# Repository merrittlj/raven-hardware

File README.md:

<h1 align="center">
    <br>
    Raven - Hardware Repository
    <br>
</h1>

## About
This is the hardware repository for the Raven smartwatch. Versioning is completely independent of the firmware repository.

## License

Distributed under the GPLv3. See ['LICENSE'](LICENSE) for more info.

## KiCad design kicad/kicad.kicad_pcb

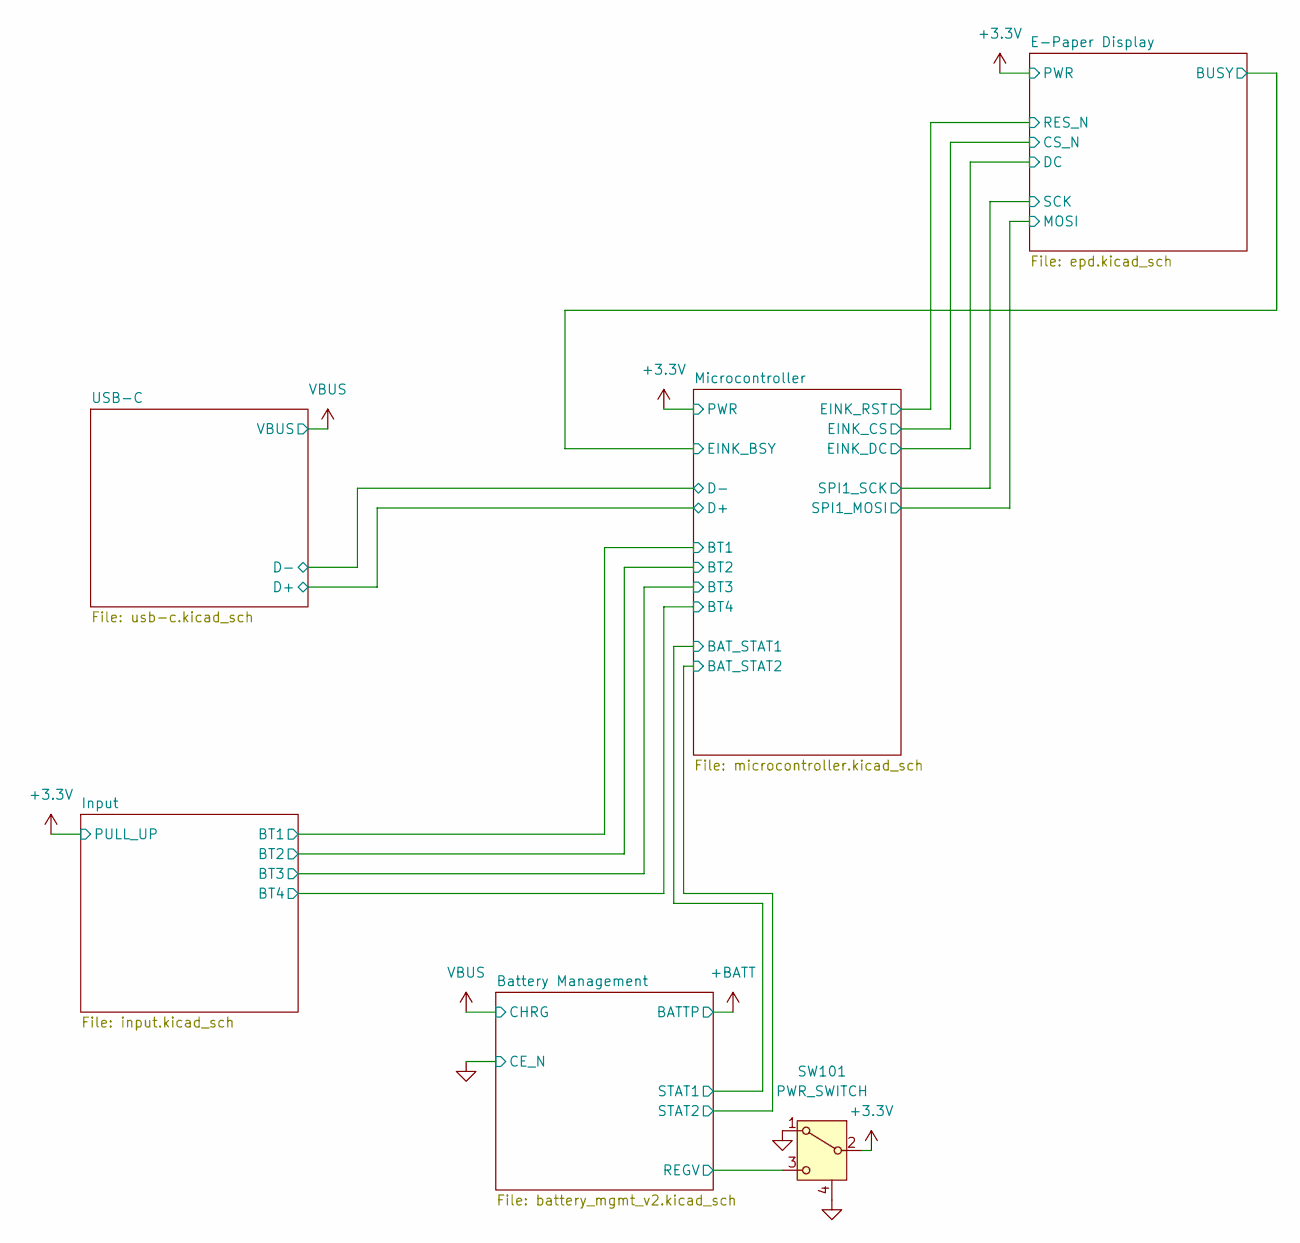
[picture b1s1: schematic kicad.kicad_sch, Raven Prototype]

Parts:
SW101: PWR_SWITCH; SSSS811101

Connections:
+3.3V: SW101.2 (B); also elsewhere on the board
/Battery Management/REGV: SW101.3 (C); also elsewhere on the board
GND: SW101.1 (A), SW101.4; also elsewhere on the board

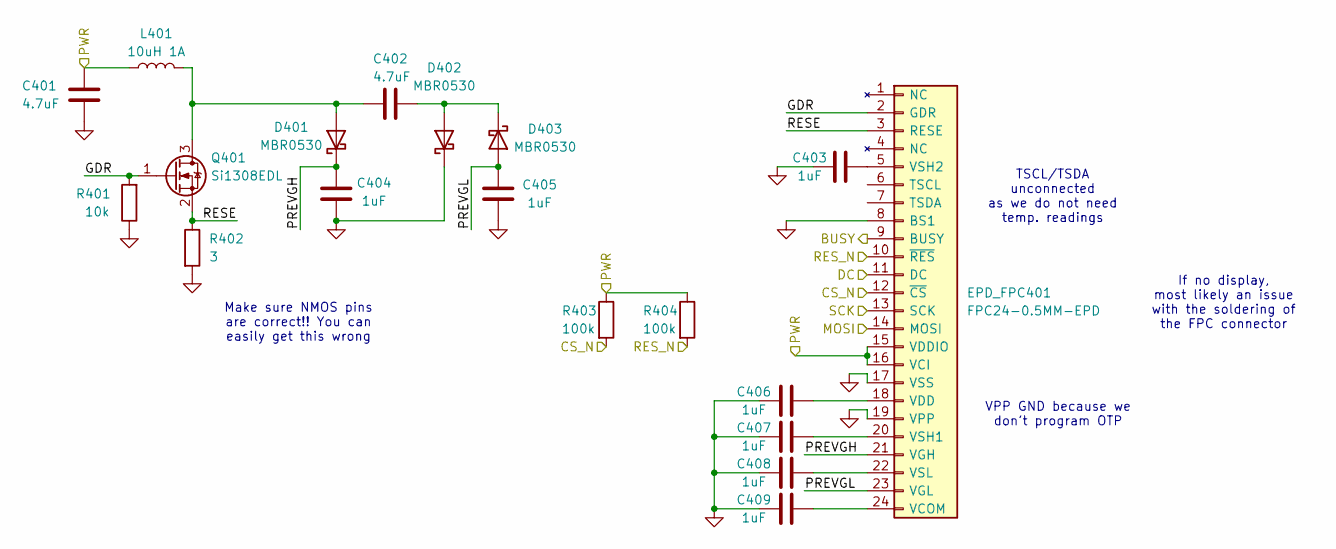
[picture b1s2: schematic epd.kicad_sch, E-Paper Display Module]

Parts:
C401, C402: 4.7uF; C_0805_2012Metric; JLC XXXXXX
C403, C404, C405, C406, C407, C408, C409: 1uF; C_0402_1005Metric; JLC 0805
D401, D402, D403: MBR0530; NSR05F40NXT5G; JLC XXXXXX
EPD_FPC401: FPC24-0.5MM-EPD; CONN_F3311A7H121024E200_AMP_FACE_UP; JLC XXXXXX
L401: 10uH 1A; IND_BOURNS_SRN3015; JLC XXXXXX
Q401: Si1308EDL; SOT-323_SC-70
R401: 10k; R_0402_1005Metric; JLC 0603
R402: 3; R_0402_1005Metric; JLC XXXXXX
R403, R404: 100k; R_0402_1005Metric; JLC 0603

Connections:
+3.3V: C401.1, EPD_FPC401.15 (VDDIO), EPD_FPC401.16 (VCI), L401.2, R403.1, R404.1; also elsewhere on the board
/E-Paper Display/BUSY: EPD_FPC401.9 (BUSY); also elsewhere on the board
/E-Paper Display/CS_N: EPD_FPC401.12 (~CS), R403.2; also elsewhere on the board
/E-Paper Display/DC: EPD_FPC401.11 (DC); also elsewhere on the board
/E-Paper Display/GDR: EPD_FPC401.2 (GDR), Q401.1 (G), R401.2
/E-Paper Display/MOSI: EPD_FPC401.14 (MOSI); also elsewhere on the board
/E-Paper Display/PREVGH: C404.2, D401.1 (K), EPD_FPC401.21 (VGH)
/E-Paper Display/PREVGL: C405.2, D403.2 (A), EPD_FPC401.23 (VGL)
/E-Paper Display/RESE: EPD_FPC401.3 (RESE), Q401.2 (S), R402.1
/E-Paper Display/RES_N: EPD_FPC401.10 (~RES), R404.2; also elsewhere on the board
/E-Paper Display/SCK: EPD_FPC401.13 (SCK); also elsewhere on the board
GND: C401.2, C403.1, C404.1, C405.1, C406.1, C407.1, C408.1, C409.1, D402.1 (K), EPD_FPC401.8 (BS1), EPD_FPC401.17 (VSS), EPD_FPC401.19 (VPP), R401.1, R402.2; also elsewhere on the board
unnamed: C402.1, D401.2 (A), L401.1, Q401.3 (D)
unnamed: C402.2, D402.2 (A), D403.1 (K)
unnamed: C409.2, EPD_FPC401.24 (VCOM)
unnamed: C406.2, EPD_FPC401.18 (VDD)
unnamed: C407.2, EPD_FPC401.20 (VSH1)
unnamed: C403.2, EPD_FPC401.5 (VSH2)
unnamed: C408.2, EPD_FPC401.22 (VSL)

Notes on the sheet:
TSCL/TSDA unconnected as we do not need temp. readings
If no display, most likely an issue with the soldering of the FPC connector
Make sure NMOS pins are correct!! You can easily get this wrong
VPP GND because we don't program OTP

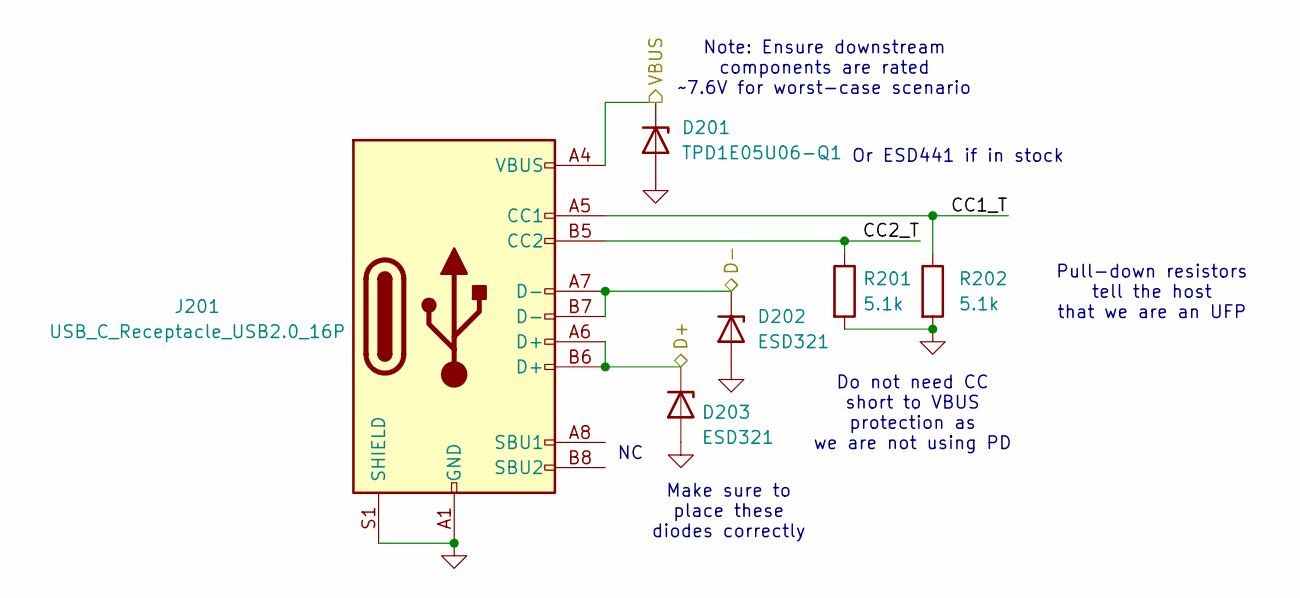
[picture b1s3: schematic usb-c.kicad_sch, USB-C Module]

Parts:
D201: TPD1E05U06-Q1; D_SOD-523; JLC XXXXXX
D202, D203: ESD321; D_SOD-523; JLC XXXXXX
J201: USB_C_Receptacle_USB2.0_16P; GCT_USB4105-GF-A-16P; JLC XXXXXX
R201, R202: 5.1k; R_0402_1005Metric; JLC 0603

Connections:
/Microcontroller/D+: D203.1 (K), J201.A6 (D+), J201.B6 (D+); also elsewhere on the board
/Microcontroller/D-: D202.1 (K), J201.A7 (D-), J201.B7 (D-); also elsewhere on the board
/USB-C/CC1_T: J201.A5 (CC1), R202.1
/USB-C/CC2_T: J201.B5 (CC2), R201.1
GND: D201.2 (A), D202.2 (A), D203.2 (A), J201.A1 (GND), J201.A12 (GND), J201.B1 (GND), J201.B12 (GND), J201.S1 (SHIELD), R201.2, R202.2; also elsewhere on the board
VBUS: D201.1 (K), J201.A4 (VBUS), J201.A9 (VBUS), J201.B4 (VBUS), J201.B9 (VBUS); also elsewhere on the board

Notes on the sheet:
Pull-down resistors tell the host that we are an UFP
Note: Ensure downstream components are rated ~7.6V for worst-case scenario
Or ESD441 if in stock
Make sure to place these diodes correctly
Do not need CC short to VBUS protection as we are not using PD

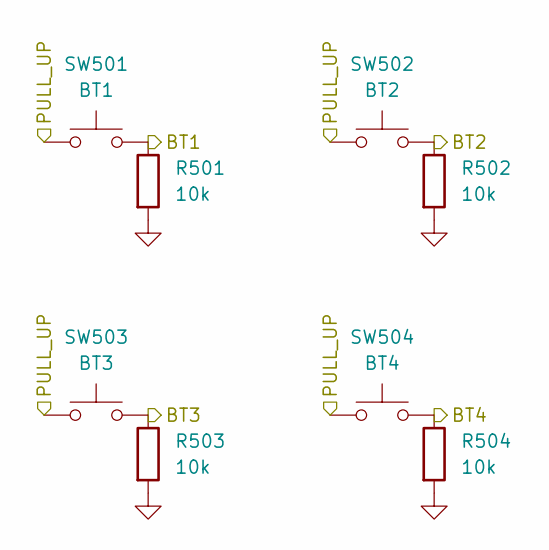
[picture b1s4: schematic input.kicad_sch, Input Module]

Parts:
R501, R502, R503, R504: 10k; R_0402_1005Metric; JLC 0603
SW501: BT1; EVQPUA; JLC XXXXXX
SW502: BT2; EVQPUA; JLC XXXXXX
SW503: BT3; EVQPUA; JLC XXXXXX
SW504: BT4; EVQPUA; JLC XXXXXX

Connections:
+3.3V: SW501.1, SW502.1, SW503.1, SW504.1; also elsewhere on the board
/Input/BT1: R501.1, SW501.2; also elsewhere on the board
/Input/BT2: R502.1, SW502.2; also elsewhere on the board
/Input/BT3: R503.1, SW503.2; also elsewhere on the board
/Input/BT4: R504.1, SW504.2; also elsewhere on the board
GND: R501.2, R502.2, R503.2, R504.2; also elsewhere on the board

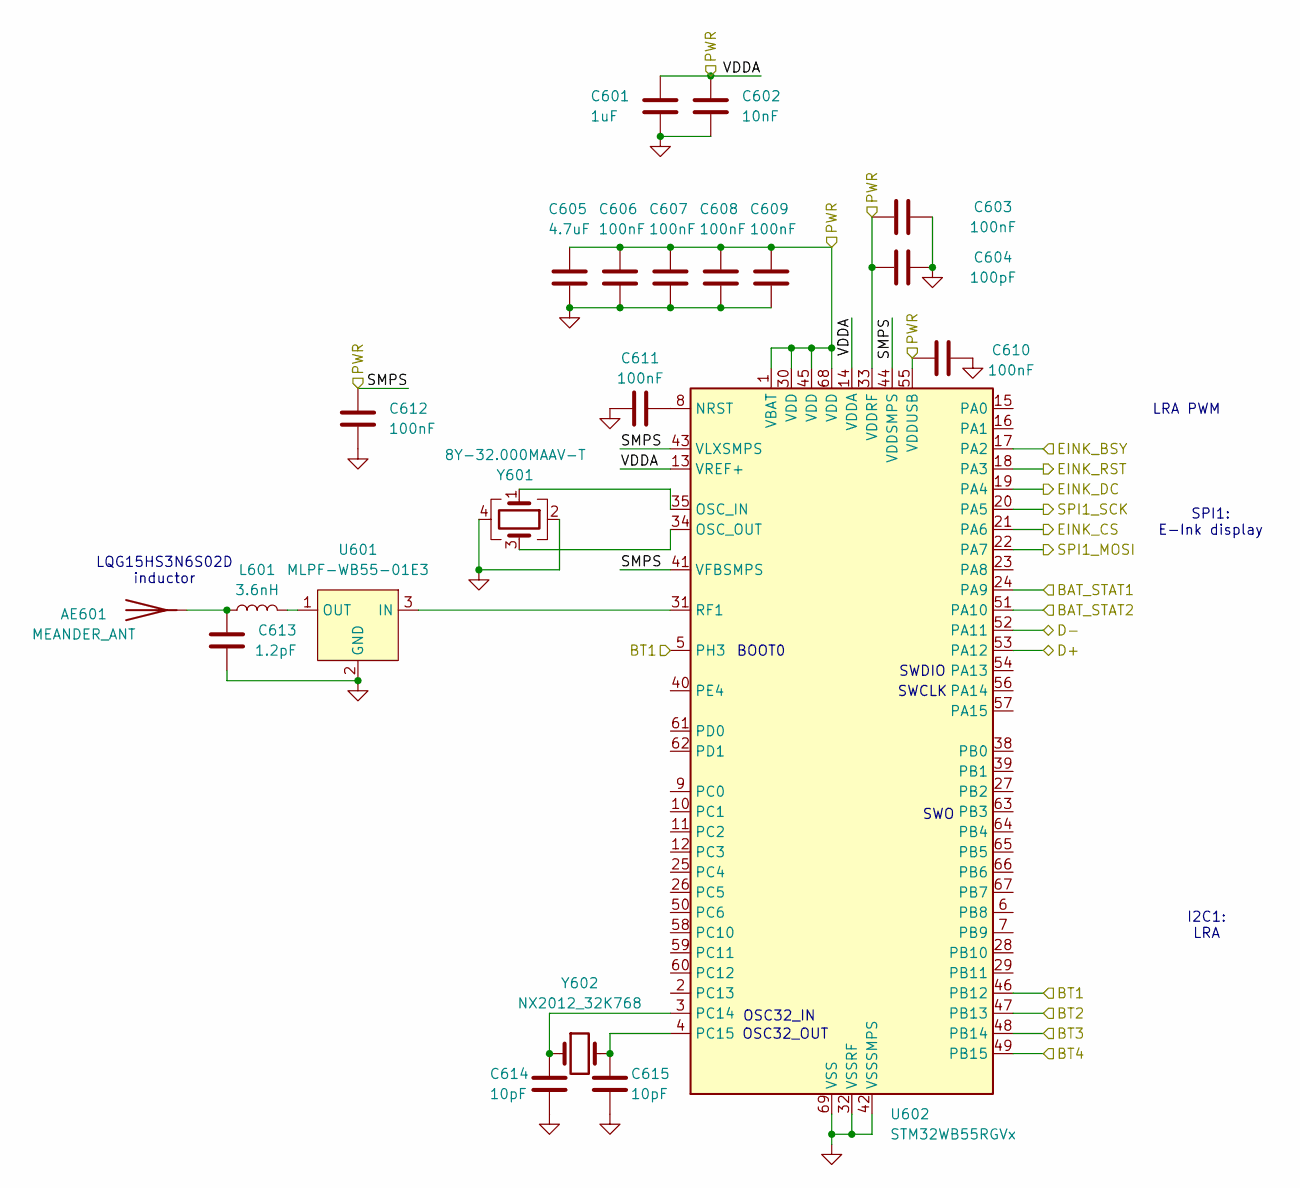
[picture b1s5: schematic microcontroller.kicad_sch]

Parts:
AE601: MEANDER_ANT; Texas_SWRA117D_2.4GHz_Right
C601: 1uF; C_0402_1005Metric
C602: 10nF; C_0402_1005Metric
C603, C606, C607, C608, C609, C610, C611, C612: 100nF; C_0402_1005Metric
C604: 100pF; C_0402_1005Metric
C605: 4.7uF; C_0402_1005Metric
C613: 1.2pF; C_0402_1005Metric
C614, C615: 10pF; C_0402_1005Metric
L601: 3.6nH; L_0402_1005Metric
U601: MLPF-WB55-01E3
U602: STM32WB55RGVx; QFN-68-1EP_8x8mm_P0.4mm_EP6.4x6.4mm
Y601: 8Y-32.000MAAV-T; XTAL_ECS-160-9-37-CKM-TR
Y602: NX2012_32K768; Crystal_SMD_2012-2Pin_2.0x1.2mm

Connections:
+3.3V: C601.1, C602.1, C603.1, C604.1, C605.1, C606.1, C607.1, C608.1, C609.1, C610.2, C612.1, U602.1 (VBAT), U602.13 (VREF+), U602.14 (VDDA), U602.30 (VDD), U602.33 (VDDRF), U602.41 (VFBSMPS), U602.43 (VLXSMPS), U602.44 (VDDSMPS), U602.45 (VDD), U602.55 (VDDUSB), U602.68 (VDD); also elsewhere on the board
/Battery Management/STAT1: U602.24 (PA9); also elsewhere on the board
/Battery Management/STAT2: U602.51 (PA10); also elsewhere on the board
/E-Paper Display/BUSY: U602.17 (PA2); also elsewhere on the board
/E-Paper Display/CS_N: U602.21 (PA6); also elsewhere on the board
/E-Paper Display/DC: U602.19 (PA4); also elsewhere on the board
/E-Paper Display/MOSI: U602.22 (PA7); also elsewhere on the board
/E-Paper Display/RES_N: U602.18 (PA3); also elsewhere on the board
/E-Paper Display/SCK: U602.20 (PA5); also elsewhere on the board
/Input/BT1: U602.5 (PH3), U602.46 (PB12); also elsewhere on the board
/Input/BT2: U602.47 (PB13); also elsewhere on the board
/Input/BT3: U602.48 (PB14); also elsewhere on the board
/Input/BT4: U602.49 (PB15); also elsewhere on the board
/Microcontroller/D+: U602.53 (PA12); also elsewhere on the board
/Microcontroller/D-: U602.52 (PA11); also elsewhere on the board
GND: C601.2, C602.2, C603.2, C604.2, C605.2, C606.2, C607.2, C608.2, C609.2, C610.1, C611.1, C612.2, C613.2, C614.2, C615.2, U601.2 (GND), U601.4 (GND), U601.5 (GND), U601.6 (GND), U602.32 (VSSRF), U602.42 (VSSSMPS), U602.69 (VSS), Y601.2, Y601.4; also elsewhere on the board
unnamed: AE601.1 (A), C613.1, L601.1
unnamed: U601.3 (IN), U602.31 (RF1)
unnamed: L601.2, U601.1 (OUT)
unnamed: C611.2, U602.8 (NRST)
unnamed: U602.35 (OSC_IN), Y601.1
unnamed: U602.34 (OSC_OUT), Y601.3
unnamed: C614.1, U602.3 (PC14), Y602.1
unnamed: C615.1, U602.4 (PC15), Y602.2

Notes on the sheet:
SWDIO
LQG15HS3N6S02D inductor
SWCLK
SWO
LRA PWM
OSC32_IN
OSC32_OUT
SPI1: E-Ink display
I2C1: LRA
BOOT0

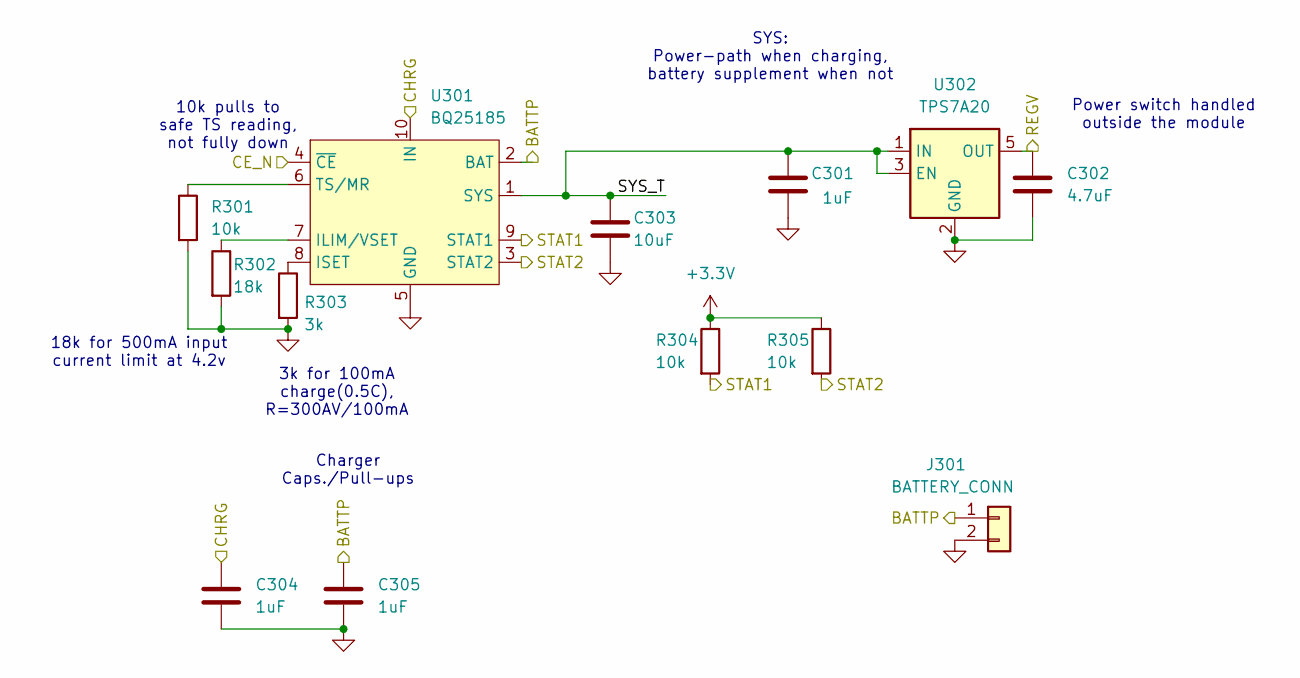
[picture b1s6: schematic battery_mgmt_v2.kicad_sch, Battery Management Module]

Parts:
C301, C304, C305: 1uF; C_0402_1005Metric
C302: 4.7uF; C_0402_1005Metric
C303: 10uF; C_0402_1005Metric
J301: BATTERY_CONN; CUSTOM_BATT_CONN; JLC XXXXXX
R301, R304, R305: 10k; R_0402_1005Metric
R302: 18k; R_0402_1005Metric
R303: 3k; R_0402_1005Metric
U301: BQ25185; WSON10_DLH_TEX-M
U302: TPS7A20; SOT-23-5

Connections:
+3.3V: R304.1, R305.1; also elsewhere on the board
+BATT: C305.1, J301.1, U301.2 (BAT)
/Battery Management/REGV: C302.1, U302.5 (OUT); also elsewhere on the board
/Battery Management/STAT1: R304.2, U301.9 (STAT1); also elsewhere on the board
/Battery Management/STAT2: R305.2, U301.3 (STAT2); also elsewhere on the board
/Battery Management/SYS_T: C301.1, C303.1, U301.1 (SYS), U302.1 (IN), U302.3 (EN)
GND: C301.2, C302.2, C303.2, C304.2, C305.2, J301.2, R301.2, R302.2, R303.2, U301.4 (~CE), U301.5 (GND), U301.11 (NC), U302.2 (GND), U302.4 (NC); also elsewhere on the board
unnamed: R302.1, U301.7 (ILIM/VSET)
unnamed: R303.1, U301.8 (ISET)
unnamed: R301.1, U301.6 (TS/MR)
VBUS: C304.1, U301.10 (IN); also elsewhere on the board

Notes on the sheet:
SYS: Power-path when charging, battery supplement when not
3k for 100mA charge(0.5C), R=300AV/100mA
Power switch handled outside the module
10k pulls to safe TS reading, not fully down
Charger Caps./Pull-ups
18k for 500mA input current limit at 4.2v

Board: 2 copper layers, 68 parts (0 on the bottom side), 44 nets, no tracks yet.

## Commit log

2024-08-16 start adding connectors
2024-08-17 connect all fpc connector pins
2024-08-17 first boost converter revision
2024-08-17 sync
2024-08-18 schem v1
2024-08-22 add debugging to v1
2024-08-23 add DA7280 symbol, rename to raven, organize schem
2024-08-24 reorganize schematic, add haptic, debug, connector module
2024-08-25 start power circuit
2024-08-25 power IC work
2024-08-26 reorganize, start usb-c
2024-08-28 start usb-c symbols
2024-08-28 finish usb esd symbol
2024-08-29 power close to completion
2024-08-31 add BQ21061
2024-09-03 modularize usb-c
2024-09-04 add datasheets, modularize current hardware
2024-09-10 add power v2, input, storage modules
2024-09-11 refactor, fix issues, ready for first design
2024-09-19 sync, almost done
2024-09-28 schematic should be finished
2024-09-30 essentially finish schematic, start adding footprints, add new footprints
2024-09-30 add button orientation and clearance
2024-10-01 fix motor with spring fingers, start PCB
2024-10-01 fix errors/update USB-c footprint, DA7280 footprint still needs fixing
2024-10-02 PCB almost finished: only battery & usb-c needed
2024-10-04 finish PCB routing, need silkscreen + checks
2024-10-04 fix and place silkscreen
2024-10-04 silkscreen art!
2024-10-05 update plot
2024-10-05 refactor usb-c module, remove unnecessary ICs
2024-10-05 finish pcb v1.0.0
2024-10-06 minor fixes, generate fab files
2024-10-07 add some assembly files, but transition towards all hand
2024-10-08 add BQ25185 symbol, start battery design with it
2024-10-09 new battery management w/ separate LDO/charger almost done
2024-10-09 slight refactoring, fix LDO power-path
2024-10-09 finish management schematic, ready for PCB
2024-10-09 finish battery PCB layout, PCB refactoring
2024-10-10 official hardware version v1.0.0, generate gerbers
2024-10-10 add LICENSE, open source
2024-12-31 Revision 2: Fix MOSFET pins and various changes
2025-01-10 Rev. 3: Fix issues
2025-01-16 Minor revisions for haptics and PCB
2025-01-27 start microcontroller schematic
2025-01-27 Start removing debug and integrate microcontroller
2025-01-28 Microcontroller additions
2025-02-03 Unfinished switch additions and fixes
2025-02-03 Small switch updates and fixes
2025-02-05 Part updates
2025-02-05 Finish microcontroller power supply
2025-02-05 Microcontroller XTAL, BMS, and Flashing connections
2025-02-05 Finish microcontroller, adding RF
2025-02-05 Footprint and MC updates
2025-02-06 Begin PCB, update footprints
2025-02-07 PCB progress
2025-02-07 Finish PCB component placement
2025-02-07 PCB Trace progress
2025-02-07 Minor schematic fixes and PCB trace progress
2025-02-08 Minor changess
2025-02-10 Update PCB for better routing of RF, USB-C, and through backside
2025-02-10 Add power/gnd vias
2025-02-11 Fix bad connections
2025-02-12 Begin EPD redo
2025-02-13 Finish flipping EPD
2025-02-18 Fix DRC errors and vias
2025-02-18 Finish silkscreen
2025-03-03 Update BOOT0
2025-03-06 V2.0.0
2025-03-06 Fix V2.0.0 files
2025-03-07 Fix tiny vias, update gerber
2025-03-07 Actually fix gerber.zip now
2025-03-26 updated pdf and BOM html
2025-04-24 v2.0.1
2025-05-09 v2.0.2
2025-05-18 Add BOM HTML
2025-09-06 start v3, complete pcb restart and remove haptics
2025-09-08 place components on pcb
2025-10-08 case revision 1
2025-10-09 case revision 2
2025-10-09 case revision 3
2025-10-10 case revision 4 wip
2025-10-12 build123d wip
2025-10-13 wip switch to build123d
2025-10-14 full build123d migration + holder additions
2025-10-16 add caps and bottom
2025-10-20 print v4
2025-10-21 print rev 5
2025-12-15 rev 6
2025-12-15 rev 7
2025-12-15 rev 8
2025-12-15 rev 9
2025-12-15 rev 10
2025-12-15 rev 11
2025-12-15 rev 12
2025-12-16 rev 13
2025-12-16 new back + power cap
